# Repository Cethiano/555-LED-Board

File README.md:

# 555-LED-Board
LED PCB board I created using the Blinky hackclub tutorial.

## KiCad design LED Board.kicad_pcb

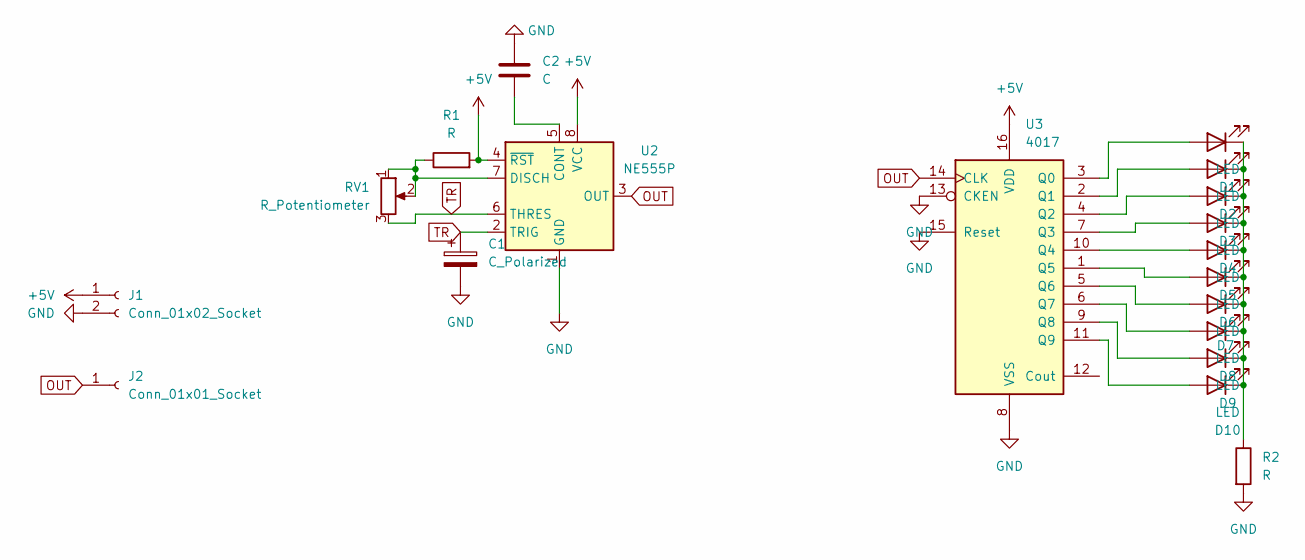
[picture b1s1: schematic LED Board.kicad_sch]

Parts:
C1: C_Polarized; CP_Radial_D5.0mm_P2.00mm
C2: C; C_Disc_D7.5mm_W2.5mm_P5.00mm
D1, D2, D3, D4, D5, D6, D7, D8, D9, D10: LED; LED_D3.0mm
J1: Conn_01x02_Socket; PinHeader_1x02_P2.54mm_Vertical
J2: Conn_01x01_Socket; PinHeader_1x01_P2.54mm_Vertical
R1, R2: R; R_Axial_DIN0207_L6.3mm_D2.5mm_P7.62mm_Horizontal
RV1: R_Potentiometer; Potentiometer_Vishay_T93YA_Vertical
U2: NE555P; DIP-8_W7.62mm
U3: 4017; N16

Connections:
+5V: J1.1, R1.2, U2.4 (~RST), U2.8 (VCC), U3.16 (VDD)
GND: C1.2, C2.1, J1.2, R2.2, U2.1 (GND), U3.8 (VSS), U3.13 (CKEN), U3.15 (Reset)
unnamed: D1.2 (A), U3.3 (Q0)
unnamed: D1.1 (K), D2.1 (K), D3.1 (K), D4.1 (K), D5.1 (K), D6.1 (K), D7.1 (K), D8.1 (K), D9.1 (K), D10.1 (K), R2.1
unnamed: D2.2 (A), U3.2 (Q1)
unnamed: D3.2 (A), U3.4 (Q2)
unnamed: D4.2 (A), U3.7 (Q3)
unnamed: D5.2 (A), U3.10 (Q4)
unnamed: D6.2 (A), U3.1 (Q5)
unnamed: D7.2 (A), U3.5 (Q6)
unnamed: D8.2 (A), U3.6 (Q7)
unnamed: D9.2 (A), U3.9 (Q8)
unnamed: D10.2 (A), U3.11 (Q9)
unnamed: C2.2, U2.5 (CONT)
unnamed: R1.1, RV1.1, RV1.2, U2.7 (DISCH)
OUT: J2.1 (Pin_1_1), U2.3 (OUT), U3.14 (CLK)
TR: C1.1, RV1.3, U2.2 (TRIG), U2.6 (THRES)

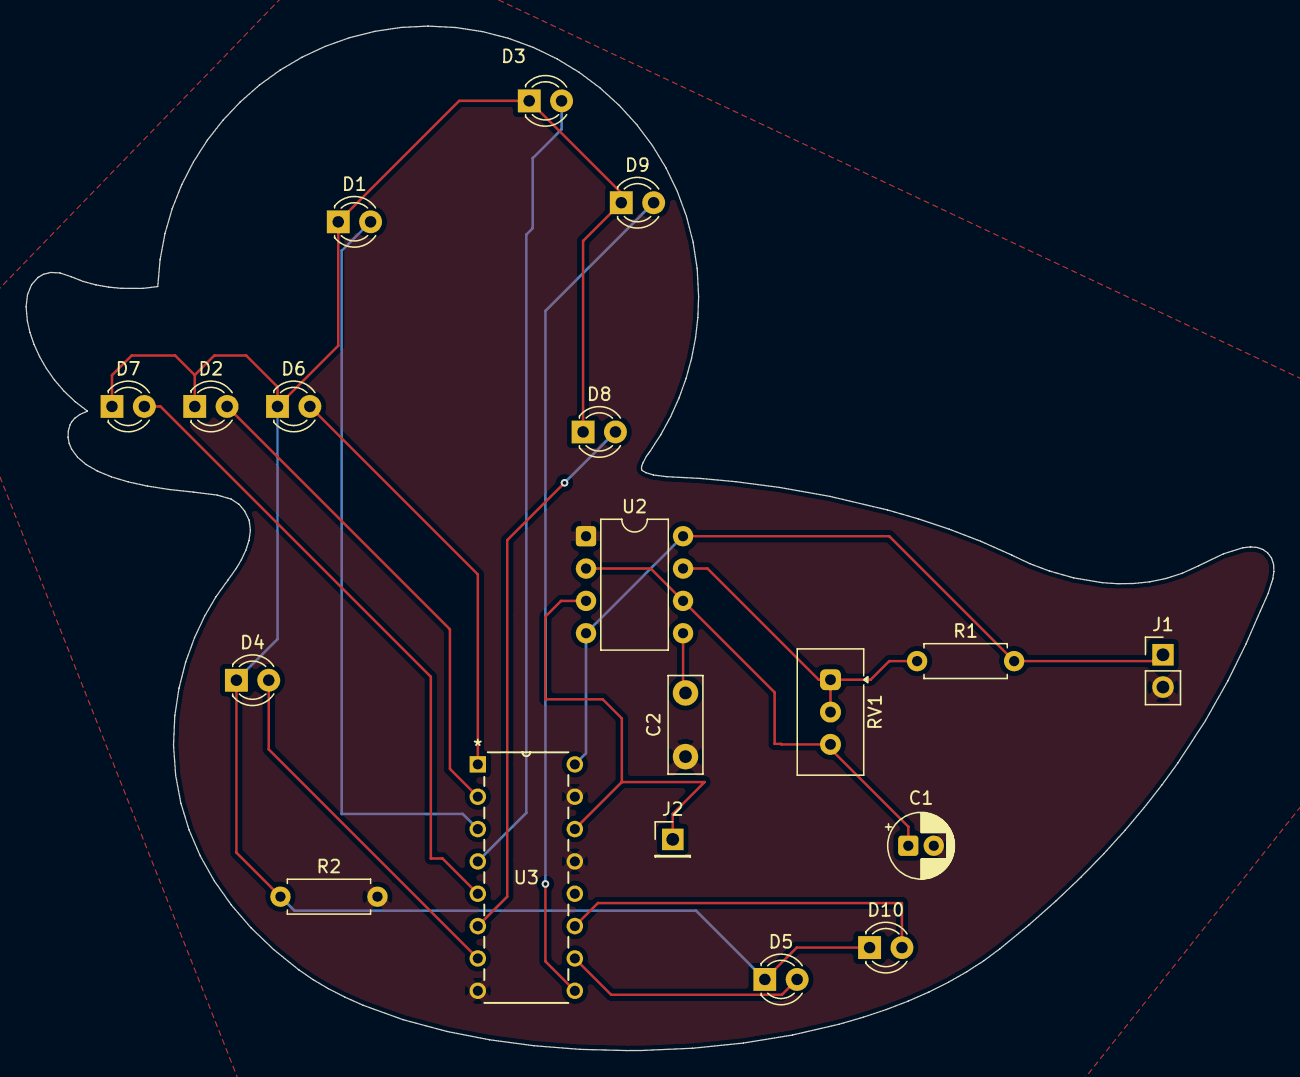
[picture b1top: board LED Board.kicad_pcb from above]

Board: 2 copper layers, 98.0 x 80.5 mm, 19 parts (0 on the bottom side), 17 nets.
